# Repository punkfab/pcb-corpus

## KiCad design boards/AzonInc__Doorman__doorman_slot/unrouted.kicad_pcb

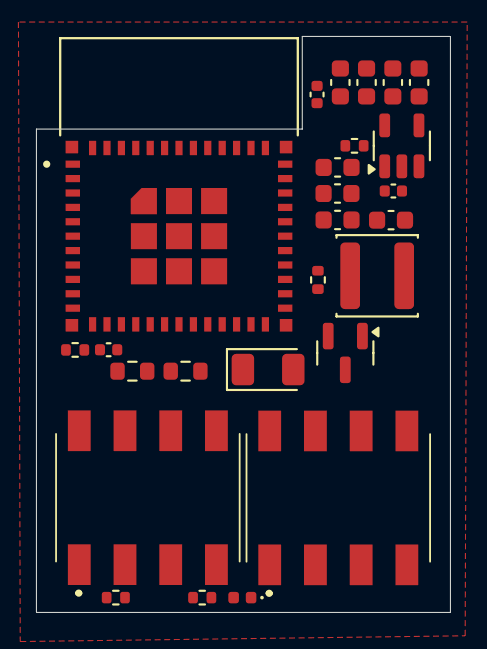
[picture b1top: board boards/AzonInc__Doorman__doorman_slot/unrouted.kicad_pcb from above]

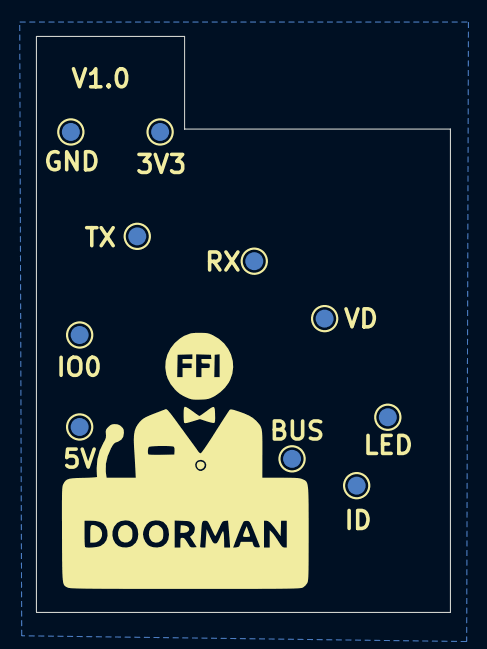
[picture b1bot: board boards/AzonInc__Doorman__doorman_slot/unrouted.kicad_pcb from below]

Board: 4 copper layers, 23.0 x 32.0 mm, 36 parts (10 on the bottom side), 22 nets, no tracks yet.

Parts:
C1, C2, C3, C4, C6, C7, C8, C9: 20uF; C_0603_1608Metric
C5, C11: 100nF; C_0402_1005Metric
C10: 20uF; C_0402_1005Metric
D1: Red; LED_0402_1005Metric
D2: D_Zener; D_1206_3216Metric
J2, J3: 70AAJ-4-M0; 70AAJ4M0
L1: TBD; L_APV_ANR4010
Q1: BC817; SOT-23
R1: 2.2K; R_0402_1005Metric
R3, R5: 10K; R_0402_1005Metric
R6: 600; R_0402_1005Metric
R7: 1M; R_0603_1608Metric
R8: 160K; R_0603_1608Metric
R9: 1K; R_0402_1005Metric
TP1: RX TestPoint; TestPoint_Pad_D1.0mm
TP2: TX TestPoint; TestPoint_Pad_D1.0mm
TP3: 3.3V TestPoint; TestPoint_Pad_D1.0mm
TP4: 5V TestPoint; TestPoint_Pad_D1.0mm
TP5: LED TestPoint; TestPoint_Pad_D1.0mm
TP6: Identity TestPoint; TestPoint_Pad_D1.0mm
TP7: VD TestPoint; TestPoint_Pad_D1.0mm
TP8: BUS TestPoint; TestPoint_Pad_D1.0mm
TP9: GND TestPoint; TestPoint_Pad_D1.0mm
TP10: GPIO0 TestPoint; TestPoint_Pad_D1.0mm
U2: XC6210B332MR; SOT-23-5
U3: ESP32-PICO-MINI-02; MODULE_ESP32-PICO-MINI-02

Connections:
+3.3V: C6.1, C7.1, C8.1, C9.1, C10.1, R5.1, TP3.1, U2.5 (VOUT), U3.3 (3V3)
+5V: J3.5, L1.1, TP4.1
GND: C1.1, C2.2, C3.2, C4.2, C5.1, C6.2, C7.2, C8.2, C9.2, C10.2, C11.1, D1.1 (K), J2.1, J2.8, Q1.2 (E), R1.1, R8.1, TP9.1, U2.2 (GND), U3.1 (GND), U3.2 (GND), U3.11 (GND), U3.14 (GND), U3.36 (GND), U3.37 (GND), U3.38 (GND), U3.39 (GND), U3.40 (GND), U3.41 (GND), U3.42 (GND), U3.43 (GND), U3.44 (GND), U3.45 (GND), U3.46 (GND), U3.47 (GND), U3.48 (GND), U3.49 (GND), U3.50 (GND), U3.51 (GND), U3.52 (GND), U3.53 (GND), U3.54 (GND), U3.55 (GND), U3.56 (GND), U3.57 (GND), U3.58 (GND), U3.59 (GND), U3.60 (GND), U3.61 (GND)
GPIO0: TP10.1, U3.23 (IO0)
GPIO4: R9.1, U3.24 (IO4)
GPIO12: J3.8, U3.19 (IO12)
GPIO13: J3.7, U3.20 (IO13)
GPIO14: J2.5, U3.18 (IO14)
GPIO15: J3.6, U3.21 (IO15)
GPIO26: R7.2, R8.2, TP7.1, U3.16 (IO26)
GPIO27: R6.2, TP5.1, U3.17 (IO27)
IDENTITY: J2.2, R1.2
unnamed: D1.2 (A), R6.1
unnamed: D2.2 (A), Q1.3 (C)
unnamed: J2.7, TP6.1
unnamed: Q1.1 (B), R9.2
unnamed: R3.2, U2.3 (CE)
unnamed: C1.2, C2.1, C3.1, C4.1, C5.2, L1.2, R3.1, U2.1 (VIN)
unnamed: C11.2, R5.2, U3.8 (EN)
RX: TP2.1, U3.30 (RXD0)
TASTA_ONLY_BUS: D2.1 (K), J2.6, R7.1, TP8.1
TX: TP1.1, U3.31 (TXD0)

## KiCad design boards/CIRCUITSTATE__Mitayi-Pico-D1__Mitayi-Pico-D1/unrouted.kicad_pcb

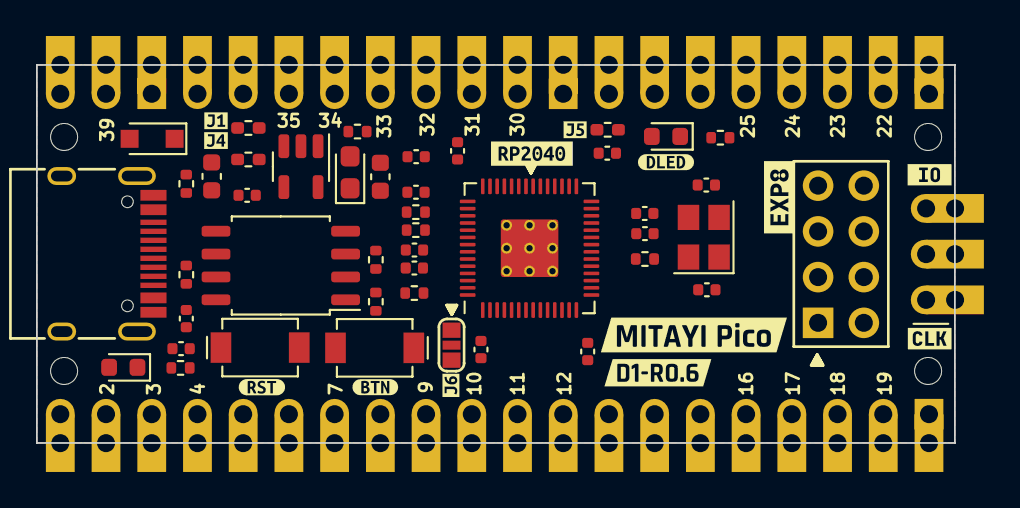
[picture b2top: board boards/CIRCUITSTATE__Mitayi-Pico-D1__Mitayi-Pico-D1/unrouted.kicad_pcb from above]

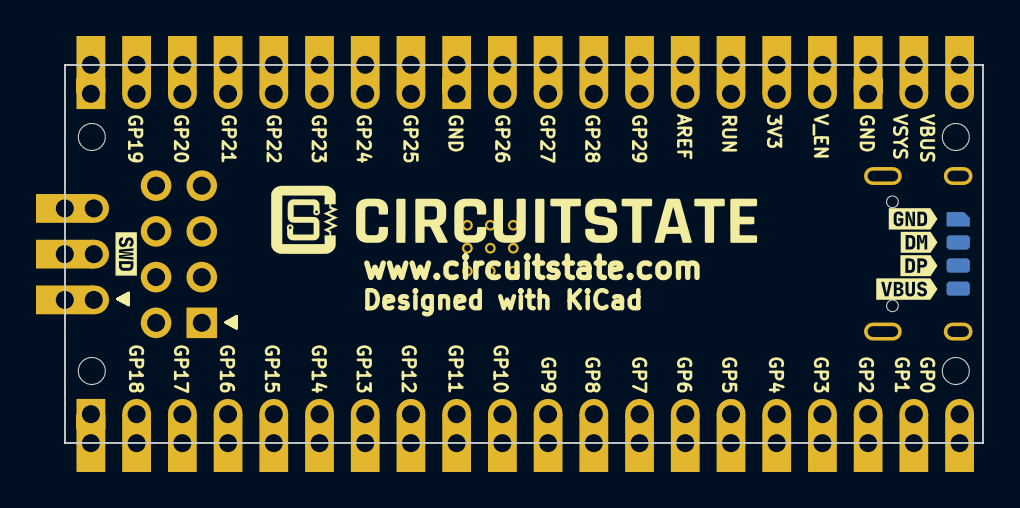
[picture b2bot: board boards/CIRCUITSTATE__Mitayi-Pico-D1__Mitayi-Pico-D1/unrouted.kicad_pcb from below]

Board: 2 copper layers, 51.0 x 21.0 mm, 73 parts (11 on the bottom side), 61 nets, no tracks yet.

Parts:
C1, C2, C6, C7, C8, C9, C10, C11, C12: 0.1uF; C_0402_1005Metric
C4, C5, C19: 1uF; C_0402_1005Metric
C13, C15: 10uF; C_0603_1608Metric
C14: 2.2uF; CP_EIA-2012-12_Kemet-R
C16: 470pF; C_0402_1005Metric
C17, C18: 30pF; C_0402_1005Metric
D1: BS5817WS; D_SOD-323_HandSoldering
D2: BLUE; LED_0603_1608Metric
D3: RED; LED_0603_1608Metric
H1, H2, H3, H4: MountingHole; MountingHole_2.2mm_M2
J1: EXP8; PinHeader_2x04_P2.54mm_Vertical
J2: USB-C-2.0; USB_C_Receptacle_HRO_TYPE-C-31-M-12
J3: Header-1; PinHeader_1x20_2H_P2.54mm_Vertical
J4: Header-2; PinHeader_1x20_2H_P2.54mm_Vertical
J5: SWD; PinHeader_1x03_P2.54mm_Vertical
J7: VBUS; Solderpad_Rounded_Rectangle_0.8x1.3mm
J8: DM; Solderpad_Rounded_Rectangle_0.8x1.3mm
J9: DP; Solderpad_Rounded_Rectangle_0.8x1.3mm
J10: GND; Solderpad_Rectangle_0.8x1.3mm_Chamfered
JP1, JP4, JP5: 0R; R_0402_1005Metric_Pad0.72x0.64mm_HandSolder
JP6: BTN_SEL; SolderJumper-3_P0.83mm_Open_Rounded-Pad_0.85x1mm
R1: DNP; R_0402_1005Metric
R2, R10: 1K; R_0402_1005Metric
R3, R4, R11: 5.1K; R_0402_1005Metric
R5, R6: 27R; R_0402_1005Metric
R7, R8: 470R; R_0402_1005Metric
R9: 10K; R_0402_1005Metric
SW1, SW2: UK-B0273-SP25Y; CK_SW_SPST_UK-B0273-SP25Y
U1: W25Q32JVSSIQ; SOIC-8_5.23x5.23mm_P1.27mm
U2: MIC5219-3.3YM5; SOT-23-5
U3: RP2040; RP2040-QFN-56
Y1: YIC-12M20P2/XT324-10/10; Crystal_SMD_3225-4Pin_3.2x2.5mm
kibuzzard-66CE1AA2: G***; kibuzzard-66CE1AA2
kibuzzard-66CE1AF9: G***; kibuzzard-66CE1AF9
kibuzzard-631DCCC7: G***; kibuzzard-631DCCC7
kibuzzard-631DCD0C: G***; kibuzzard-631DCD0C
kibuzzard-631DCDA0: G***; kibuzzard-631DCDA0
kibuzzard-631DCDB3: G***; kibuzzard-631DCDB3
kibuzzard-631DCE60: G***; kibuzzard-631DCE60
kibuzzard-632CA15B: G***; kibuzzard-632CA15B
kibuzzard-660C3D9D: G***; kibuzzard-660C3D9D
kibuzzard-680DBD8D: G***; kibuzzard-680DBD8D
kibuzzard-680DBD83: G***; kibuzzard-680DBD83
kibuzzard-680DBD88: G***; kibuzzard-680DBD88
kibuzzard-680DBD96: G***; kibuzzard-680DBD96
kibuzzard-680DBDCE: G***; kibuzzard-680DBDCE
kibuzzard-680DBDF9: G***; kibuzzard-680DBDF9
kibuzzard-680DC314: G***; kibuzzard-680DC314
kibuzzard-680DC361: G***; kibuzzard-680DC361
kibuzzard-66126165: G***; kibuzzard-66126165

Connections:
+1V1: C2.1, C4.1, U3.23 (DVDD), U3.45 (VREG-VOUT), U3.50 (DVDD)
+3V3: C1.1, C5.1, C6.1, C7.1, C8.1, C9.1, C10.1, C11.1, C12.1, C14.1, C15.1, D3.2 (A), J1.2, J4.5, JP1.2 (B), R1.1, R9.1, R11.2, U1.8 (VCC), U2.5 (OUT), U3.1 (IOVDD), U3.10 (IOVDD), U3.22 (IOVDD), U3.33 (IOVDD), U3.42 (IOVDD), U3.44 (VREG-VIN), U3.48 (USB-VDD), U3.49 (IOVDD)
/AREF: J4.6, JP1.1 (A), U3.43 (ADC-AVDD)
/GPIO0: J3.1, U3.2 (GPIO0)
/GPIO1: J3.2, U3.3 (GPIO1)
/GPIO2: J3.3, JP6.3 (B), R11.1, U3.4 (GPIO2)
/GPIO3: J3.4, U3.5 (GPIO3)
/GPIO4: J3.5, U3.6 (GPIO4)
/GPIO5: J3.6, U3.7 (GPIO5)
/GPIO6: J3.7, U3.8 (GPIO6)
/GPIO7: J3.8, U3.9 (GPIO7)
/GPIO8: J1.7, J3.9, U3.11 (GPIO8)
/GPIO9: J1.8, J3.10, U3.12 (GPIO9)
/GPIO10: J3.11, U3.13 (GPIO10)
/GPIO11: J3.12, U3.14 (GPIO11)
/GPIO12: J1.3, J3.13, U3.15 (GPIO12)
/GPIO13: J1.4, J3.14, U3.16 (GPIO13)
/GPIO14: J1.6, J3.15, U3.17 (GPIO14)
/GPIO15: J1.5, J3.16, U3.18 (GPIO15)
/GPIO16: J3.17, U3.27 (GPIO16)
/GPIO17: J3.18, U3.28 (GPIO17)
/GPIO18: J3.19, U3.29 (GPIO18)
/GPIO19: J4.19, U3.30 (GPIO19)
/GPIO20: J4.18, U3.31 (GPIO20)
/GPIO21: J4.17, U3.32 (GPIO21)
/GPIO22: J4.16, U3.34 (GPIO22)
/GPIO23: J4.15, U3.35 (GPIO23)
/GPIO24: J4.14, U3.36 (GPIO24)
/GPIO25: J4.13, JP5.1 (A), U3.37 (GPIO25)
/GPIO26: J4.11, U3.38 (GPIO26/ADC0)
/GPIO27: J4.10, U3.39 (GPIO27/ADC1)
/GPIO28: J4.9, U3.40 (GPIO28/ADC2)
/GPIO29: J4.8, U3.41 (GPIO29/ADC3)
/QSPI_SCLK: U1.6 (CLK), U3.52 (QSPI-SCLK)
/QSPI_SD0: U1.5 (DI(IO0)), U3.53 (QSPI-SD0)
/QSPI_SD1: U1.2 (DO(IO1)), U3.55 (QSPI-SD1)
/QSPI_SD2: U1.3 (IO2), U3.54 (QSPI-SD2)
/QSPI_SD3: U1.7 (IO3), U3.51 (QSPI-SD3)
/QSPI_SS: R1.2, R2.1, U1.1 (~CS), U3.56 (QSPI-SS-N)
/RUN: C19.1, J4.7, R9.2, SW1.1, U3.26 (RUN)
/SWCLK: J5.1, U3.24 (SWCLK)
/SWDIO: J5.3, U3.25 (SWDIO)
/USB_D+: J2.A6 (D+), J2.B6 (D+), J9.1, R5.1
/USB_D-: J2.A7 (D-), J2.B7 (D-), J8.1, R6.1
/VSYS: C13.1, D1.1 (K), J4.2, JP4.1 (A), U2.1 (IN)
/V_EN: J4.4, JP4.2 (B), U2.3 (EN)
/XIN: C17.1, U3.20 (XIN), Y1.1
/XOUT: R10.1, U3.21 (XOUT)
/~USB_BOOT: JP6.1 (A), R2.2
GND: C1.2, C2.2, C4.2, C5.2, C6.2, C7.2, C8.2, C9.2, C10.2, C11.2, C12.2, C13.2, C14.2, C15.2, C16.2, C17.2, C18.2, C19.2, J1.1, J2.A1 (GND), J2.A12 (GND), J2.B1 (GND), J2.B12 (GND), J2.S1 (SHIELD), J3.20, J4.3, J4.12, J4.20, J5.2, J10.1, R3.2, R4.2, R7.1, R8.1, SW1.2, SW2.2, U1.4 (GND), U2.2 (GND), U3.19 (TESTEN), U3.57 (GND), Y1.2, Y1.4
unnamed: C18.1, R10.2, Y1.3
unnamed: D2.2 (A), JP5.2 (B)
unnamed: D2.1 (K), R7.2
unnamed: D3.1 (K), R8.2
unnamed: J2.A5 (CC1), R3.1
unnamed: J2.B5 (CC2), R4.1
unnamed: JP6.2 (C), SW2.1
unnamed: C16.1, U2.4 (BP)
unnamed: R6.2, U3.46 (USB-DM)
unnamed: R5.2, U3.47 (USB-DP)
VBUS: D1.2 (A), J2.A4 (VBUS), J2.A9 (VBUS), J2.B4 (VBUS), J2.B9 (VBUS), J4.1, J7.1

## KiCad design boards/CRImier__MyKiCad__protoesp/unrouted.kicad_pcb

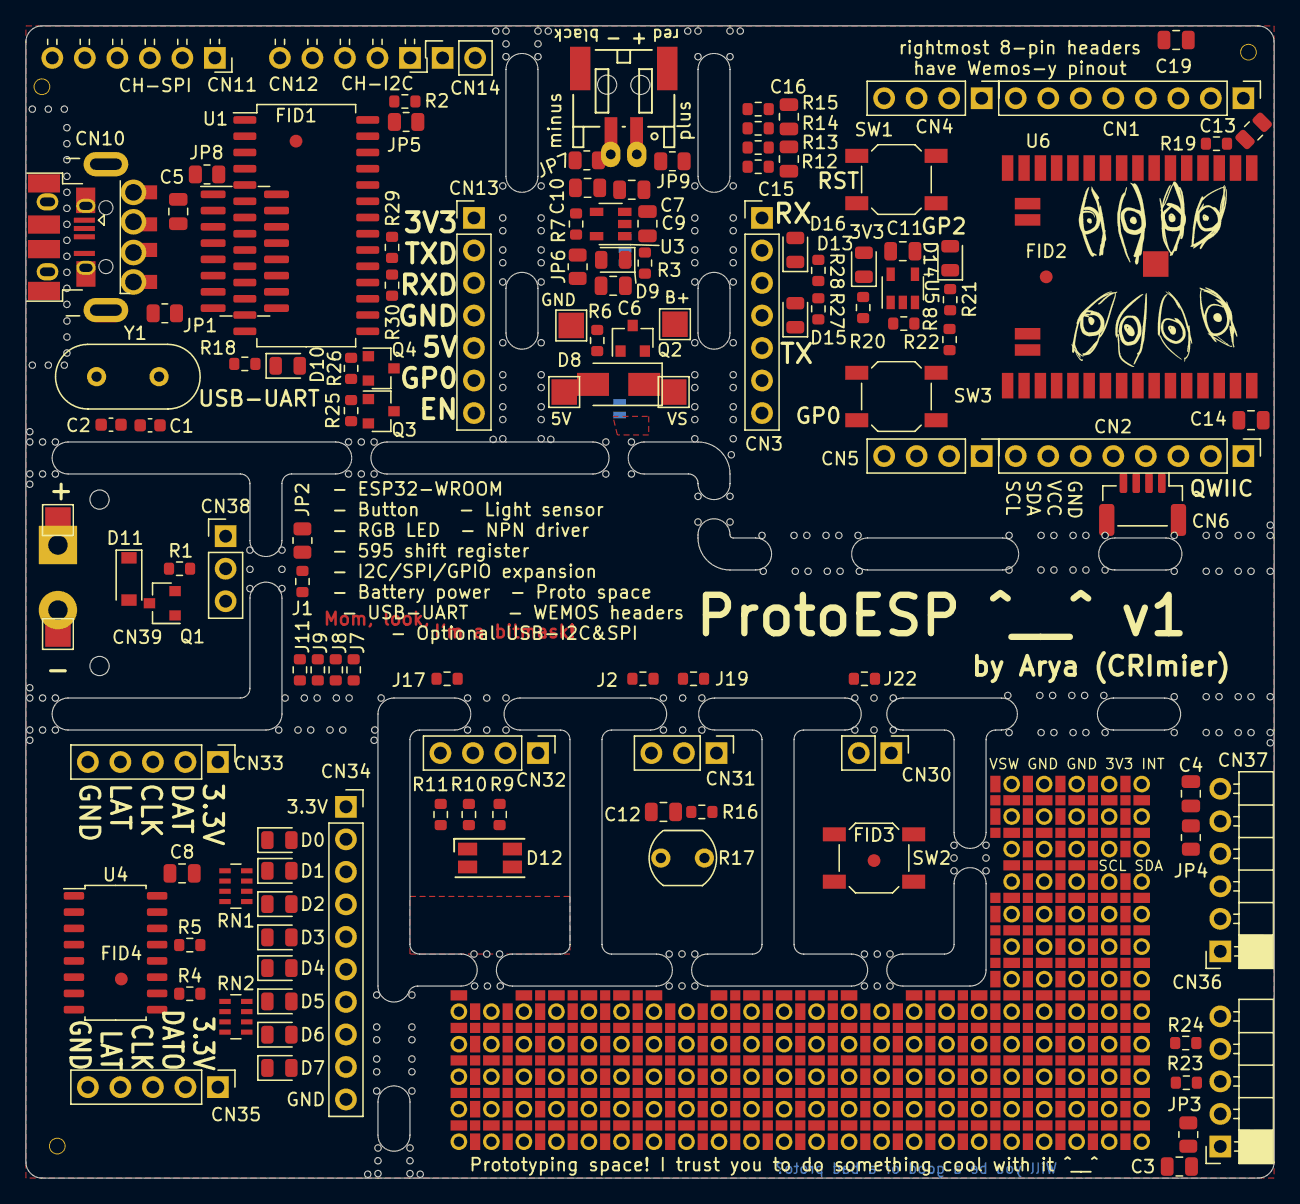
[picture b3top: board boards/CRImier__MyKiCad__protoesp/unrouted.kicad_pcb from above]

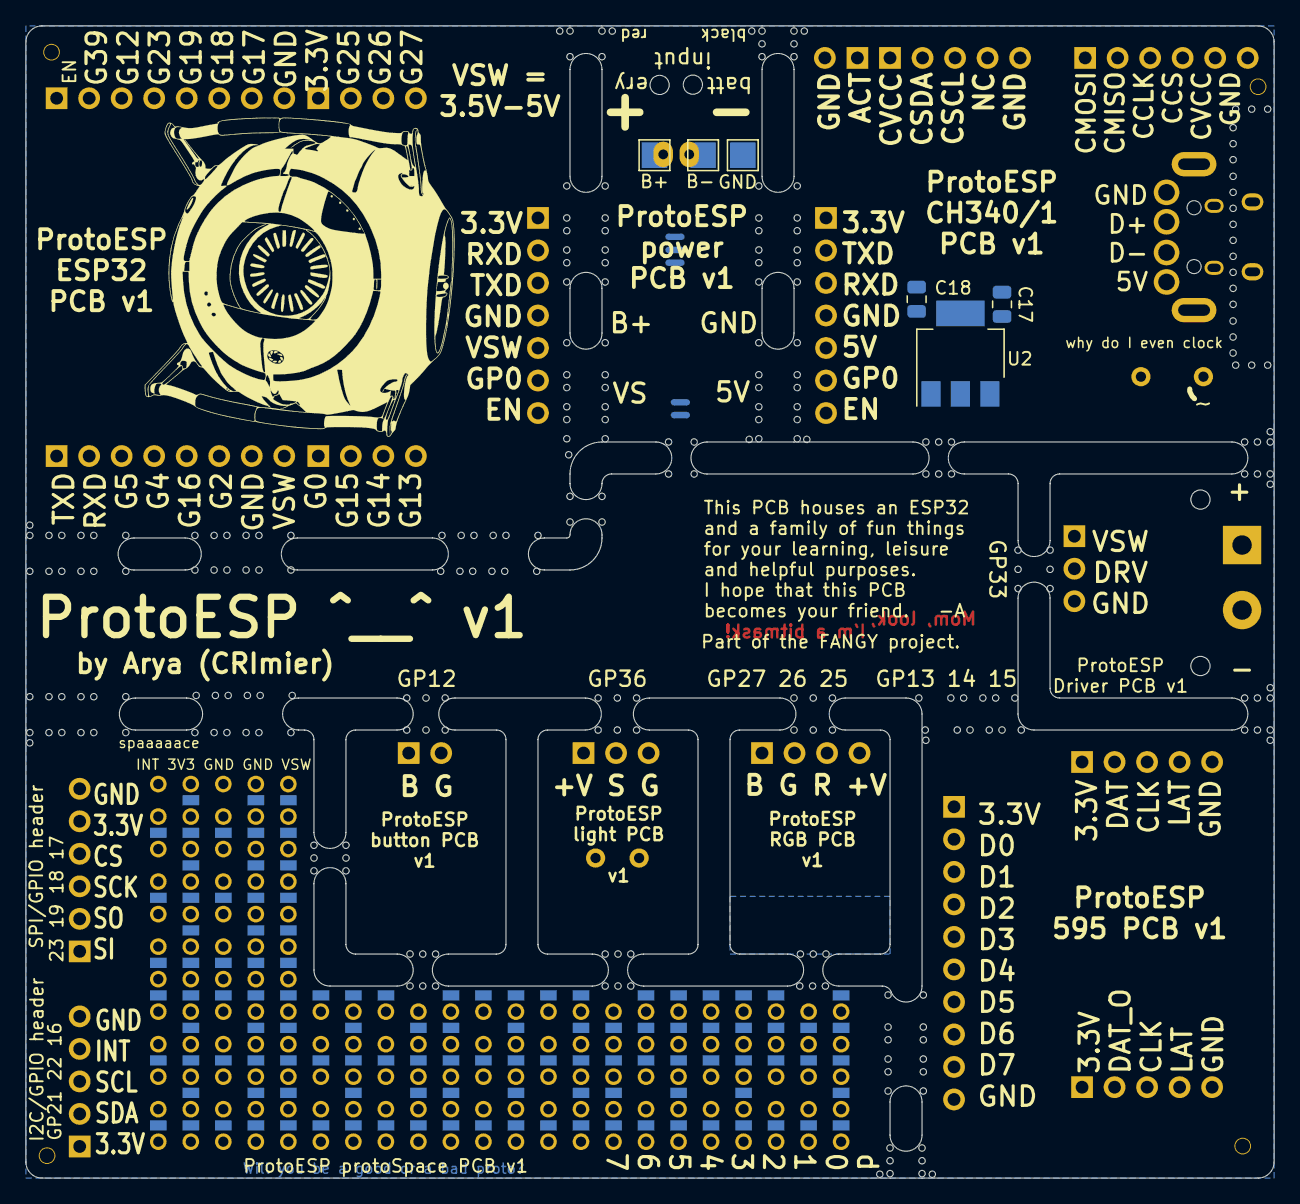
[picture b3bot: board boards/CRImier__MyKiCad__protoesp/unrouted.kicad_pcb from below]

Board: 2 copper layers, 97.5 x 90.0 mm, 149 parts (11 on the bottom side), 104 nets, no tracks yet.

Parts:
C1, C2: 18pF; C_0603_1608Metric
C3, C4, C5, C7, C8, C11, C12, C14, C15, C16, C17, C18, C19: 100nF; C_0805_2012Metric
C6, C9, C10, C13: 1uF; C_0805_2012Metric
CN1: EPINS_TOP; PinHeader_1x08_P2.54mm_Vertical
CN2: EPINS_BOTTOM; PinHeader_1x08_P2.54mm_Vertical
CN3: ESP_PROG; PinHeader_1x07_P2.54mm_Vertical
CN4: EPINS_TOP_E; PinHeader_1x04_P2.54mm_Vertical
CN5: EPINS_BOTTOM_E; PinHeader_1x04_P2.54mm_Vertical
CN6: QWIIC; JST_SH_BM04B-SRSS-TB_1x04-1MP_P1.00mm_Vertical
CN10: USB_CURSED; USB_Combined
CN11: CH_SPI; PinSocket_1x06_P2.54mm_Horizontal
CN12: CH_I2C; PinSocket_1x05_P2.54mm_Horizontal
CN13: CH341_PROG; PinHeader_1x07_P2.54mm_Vertical
CN14: CH_PROG; PinSocket_1x02_P2.54mm_Vertical
CN20: BATT; JST_PH_S2B-PH-SM4-TB_02x2.00mm_Angled
CN30: BUTTON_CONN; PinHeader_1x02_P2.54mm_Vertical
CN31: LDR_CONN; PinHeader_1x03_P2.54mm_Vertical
CN32: RGB_CONN; PinHeader_1x04_P2.54mm_Vertical
CN33: 595_CONN; PinHeader_1x05_P2.54mm_Vertical
CN34: 595_OUTS; PinSocket_1x10_P2.54mm_Vertical
CN35: 595CHAIN_CONN; PinHeader_1x05_P2.54mm_Vertical
CN36: E_I2C; PinSocket_1x05_P2.54mm_Horizontal
CN37: E_SPI; PinSocket_1x06_P2.54mm_Horizontal
CN38: DRV_CONN; PinHeader_1x03_P2.54mm_Vertical
CN39: DRV; TerminalBlock_bornier-2_P5.08mm
D0, D1, D2, D3, D4, D5, D6, D7: LED; LED_0805_2012Metric
D8: SS14; D_SMA
D9: LED_CHG; LED_0805_2012Metric
D10: LED_5V; LED_0805_2012Metric
D11: 1N4148; D_SOD-123
D12: LED_RGBA; LED_RGB_1210
D13: LED_3V3; LED_0805_2012Metric
D14: LED_ESP; LED_0805_2012Metric
D15: LED_TX; LED_0805_2012Metric
D16: LED_RX; LED_0805_2012Metric
FID1, FID2, FID3, FID4: Fiducial; Fiducial_1mm_Mask2mm
H1, H1#2, H1#3, H1#5: pin_hole; PinHole_1,5mm
H1#4, H4: MountingHole; JLCPCBToolingHole
H2, H3: ToolingHole; JLCPCBToolingHole
J1, J2, J7, J8, J9, J11, J17, J19, J22: 0R; R_0603_1608Metric
JP1, JP2, JP3, JP4, JP5, JP7, JP8, JP9: 0R; R_0805_2012Metric
JP6: F; R_0805_2012Metric
NT1, NT2, NT3, NT6, NT7: Net-Tie_2; NetTie-2_SMD_Pad0.5mm
P1: PROTO_SPACE; PROTO_THT_SMD_FULL
Q1, Q3, Q4: BC817; SOT-23
Q2: CJ2305; SOT-23
R1, R2, R3, R4, R5, R6, R18, R20, R21, R23, R24, R27, R28, R29, R30: 1K8; R_0603_1608Metric
R7, R8, R16, R19, R22, R25, R26: 4K7; R_0603_1608Metric
R9: RGB_R_B; R_0603_1608Metric
R10: RGB_R_G; R_0603_1608Metric
R11: RGB_R_R; R_0603_1608Metric
R12, R13, R14, R15: 47K; R_0603_1608Metric
R17: LDR07; R_LDR_5.1x4.3mm_P3.4mm_Vertical
RN1, RN2: R_Pack04; R_Array_Concave_4x0603
SW1: EN; SW_SPST_SKQG_WithStem
SW2: BUTTON; SW_SPST_SKQG_WithStem
SW3: GP0; SW_SPST_SKQG_WithStem
TP1: +; TestPoint_Pad_2.0x2.0mm
TP2: -; TestPoint_Pad_2.0x2.0mm
TP3, TP8: B+; TestPoint_Pad_2.0x2.0mm
TP4: 5V; TestPoint_Pad_2.0x2.0mm
TP5, TP9: GND; TestPoint_Pad_2.0x2.0mm
TP6: VS; TestPoint_Pad_2.0x2.0mm
TP7: B-; TestPoint_Pad_2.0x2.0mm
U1: CH341; SOIC-28W_SOIC16_CH34x_Combined
U2: AP1117-33; SOT-223-3_TabPin2
U3: LTH7R; SOT-23-5
U4: 74HC595; SOP-16_4.55x10.3mm_P1.27mm
U5: AP2112K-3.3; SOT-23-5
U6: ESP32-WROOM-32
Y1: 12MHz; Crystal_HC49-U_Vertical

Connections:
595_CLK: CN5.3, J9.1, U6.13 (IO14)
595_CLK_J: CN33.3, CN35.3, J9.2, U4.11 (SRCLK)
595_DAT: CN5.4, J8.1, U6.16 (IO13)
595_DAT_J: CN33.2, J8.2, U4.14 (SER)
595_DAT_O: CN35.2, U4.9 (QH')
595_LAT: CN5.2, J11.1, U6.23 (IO15)
595_LAT_J: CN33.4, CN35.4, J11.2, U4.12 (RCLK)
+3V3: C11.1, C13.1, C14.1, C18.1, CN1.8, CN3.1, CN6.2, CN13.1, D13.2 (A), D14.2 (A), D15.2 (A), D16.2 (A), J2.2, J7.1, J17.2, JP3.1, JP4.1, JP5.2, NT1.1, NT1.2, P1.d, R19.1, R22.2, R23.2, R24.2, U2.2 (VO), U5.5 (VOUT), U6.2 (VDD)
+5V: C6.1, C17.1, CN13.5, D8.2 (A), D10.2 (A), JP1.1, JP6.1, Q2.1 (G), R6.2, TP4.1, U2.3 (VI)
+BATT: C9.1, JP9.1, Q2.3 (D), R15.2, TP3.1, U3.3 (BAT)
+VSW: CN2.8, CN3.5, D8.1 (K), JP2.1, P1.a, Q2.2 (S), R8.1, TP6.1, U5.1 (VIN)
-BATT: CN20.2, JP7.1, TP7.1
/5D0: CN34.2, D0.2 (A), P1.d0, U4.15 (QA)
/5D1: CN34.3, D1.2 (A), P1.d1, U4.1 (QB)
/5D2: CN34.4, D2.2 (A), P1.d2, U4.2 (QC)
/5D3: CN34.5, D3.2 (A), P1.d3, U4.3 (QD)
/5D4: CN34.6, D4.2 (A), P1.d4, U4.4 (QE)
/5D5: CN34.7, D5.2 (A), P1.d5, U4.5 (QF)
/5D6: CN34.8, D6.2 (A), P1.d6, U4.6 (QG)
/5D7: CN34.9, D7.2 (A), P1.d7, U4.7 (QH)
/BUTTON_J: CN30.1, J22.2, SW2.1
/CH_XI: C1.1, U1.13 (XI), Y1.1
/CH_XO: C2.1, U1.14 (XO), Y1.2
/LIGHT_J: C12.1, CN31.2, J19.2, R16.1, R17.1
BATT_IN+: CN20.1, JP9.2, TP8.1
BUTTON: CN5.1, J22.1, U6.14 (IO12)
CHG_VIN: C7.1, C10.1, D9.2 (A), JP6.2, R12.2, U3.4 (VCC)
CH_ACT: CN14.1, R2.2
CH_CLK: CN11.3, U1.18 (~DCD/D3/SCK)
CH_CS: CN11.4, U1.15 (CS0/D0/~CTS)
CH_EN: CN13.7, NT7.1, Q3.3 (C)
CH_GP0: CN13.6, NT6.1, Q4.3 (C)
CH_MISO: CN11.2, U1.22 (~SLP/D7/DIN)
CH_MOSI: CN11.1, Q4.2 (E), R25.1, U1.20 (~DTR/D5/DOUT)
CH_RXD: CN13.3, NT3.1, R30.1
CH_SCL: CN12.3, U1.24 (SCL)
CH_SDA: CN12.2, U1.23 (SDA)
CH_TXD: CN13.2, NT2.1, R29.1
CH_V3: C5.1, JP8.2, U1.9 (V3)
CH_VCC: CN11.5, CN12.1, JP5.1, JP8.1, U1.28 (VCC)
CH_~RTS: CN12.4, Q3.2 (E), R26.1, U1.21 (~RTS/D6/DIN2)
D+: CN10.3 (D+), U1.10 (UD+)
D-: CN10.2 (D-), U1.11 (UD-)
DRIVER: J1.2, U6.9 (IO33)
DRV+: CN38.1, CN39.1, D11.1 (K), JP2.2, TP1.1
DRV-: CN39.2, D11.2 (A), Q1.3 (C), TP2.1
E_CS: CN1.7, CN37.4, U6.28 (IO17)
E_EN: C19.1, CN1.1, CN3.7, NT7.2, R19.2, SW1.2, U6.3 (EN)
E_GP0: CN3.6, NT6.2, R22.1, SW3.2, U6.25 (IO0)
E_INT: CN2.5, CN36.4, P1.e, U6.27 (IO16)
E_MISO: CN1.5, CN37.2, U6.31 (IO19)
E_MOSI: CN1.4, CN37.1, U6.37 (IO23)
E_RXD: CN2.2, CN3.2, NT2.2, R28.1, U6.34 (RXD0/IO3)
E_SCK: CN1.6, CN37.3, U6.30 (IO18)
E_SCL: CN6.4, CN36.3, P1.f, R24.1, U6.36 (IO22)
E_SDA: CN6.3, CN36.2, P1.g, R23.1, U6.33 (IO21)
E_TXD: CN2.1, CN3.3, NT3.2, R27.1, U6.35 (TXD0/IO1)
GND: C1.2, C2.2, C3.2, C4.2, C5.2, C6.2, C7.2, C8.2, C9.2, C10.2, C11.2, C12.2, C13.2, C14.2, C15.2, C16.2, C17.2, C18.2, C19.2, CN2.7, CN3.4, CN4.1, CN6.1, CN6.MP (MountPin), CN10.4 (GND), CN10.5 (Shield), CN11.6, CN12.5, CN13.4, CN14.2, CN20.MP (MountPin), CN30.2, CN31.3, CN33.5, CN34.10, CN35.5, CN36.5, CN37.6, CN38.3, JP7.2, P1.b, P1.c, Q1.2 (E), R5.1, R6.1, R7.1, R13.2, R14.2, R17.2, R18.1, R20.1, RN1.1 (R1.1), RN1.2 (R2.1), RN1.3 (R3.1), RN1.4 (R4.1), RN2.1 (R1.1), RN2.2 (R2.1), RN2.3 (R3.1), RN2.4 (R4.1), SW1.1, SW2.2, SW3.1, TP5.1, TP9.1, U1.12 (GND), U2.1 (GND), U3.2 (GND), U4.8 (GND), U5.2 (GND), U6.1 (GND), U6.15 (GND), U6.38 (GND), U6.39 (GND)
IO4: CN2.4, U6.26 (IO4)
IO5: CN2.3, U6.29 (IO5)
IO32: CN1.3, U6.8 (IO32)
IO39: CN1.2, U6.5 (SENSOR_VN)
LED_BLUE: CN4.4, CN32.1, R9.2, U6.12 (IO27)
LED_ESP: CN2.6, R21.1, U6.24 (IO2)
LED_GREEN: CN4.3, CN32.2, R10.2, U6.11 (IO26)
LED_RED: CN4.2, CN32.3, R11.2, U6.10 (IO25)
LED_VCC: CN32.4, D12.4 (A), J17.1
LIGHT: J19.1, U6.4 (SENSOR_VP)
unnamed: C3.1, CN36.1, JP3.2
unnamed: C4.1, CN37.5, JP4.2
unnamed: CN10.1 (VBUS), JP1.2
unnamed: CN31.1, J2.1, R16.2
unnamed: CN38.2, J1.1, R1.1
unnamed: D0.1 (K), RN1.8 (R1.2)
unnamed: D1.1 (K), RN1.7 (R2.2)
unnamed: D2.1 (K), RN1.6 (R3.2)
unnamed: D3.1 (K), RN1.5 (R4.2)
unnamed: D4.1 (K), RN2.8 (R1.2)
unnamed: D5.1 (K), RN2.7 (R2.2)
unnamed: D6.1 (K), RN2.6 (R3.2)
unnamed: D7.1 (K), RN2.5 (R4.2)
unnamed: D9.1 (K), R3.2
unnamed: D10.1 (K), R18.2
unnamed: D12.1 (RK), R11.1
unnamed: D12.2 (GK), R10.1
unnamed: D12.3 (BK), R9.1
unnamed: D13.1 (K), R20.2
unnamed: D14.1 (K), R21.2
unnamed: D15.1 (K), R27.2
unnamed: D16.1 (K), R28.2
unnamed: Q1.1 (B), R1.2
unnamed: Q3.1 (B), R25.2
unnamed: Q4.1 (B), R26.2
unnamed: R2.1, U1.1 (~ACT)
unnamed: R3.1, U3.1 (CHRG)
unnamed: R4.2, U4.10 (~SRCLR)
unnamed: R5.2, U4.13 (~OE)
unnamed: R7.2, U3.5 (PROG)
unnamed: R8.2, U5.3 (EN)
RXD: R30.2, U1.6 (RXD/PEMP)
TXD: R29.2, U1.5 (TXD/~ERR)
VBAT: C16.1, R14.1, R15.1, U6.7 (IO35)
VCC_595: C8.1, CN33.1, CN34.1, CN35.1, J7.2, R4.1, U4.16 (VCC)
VUSB: C15.1, R12.1, R13.1, U6.6 (IO34)

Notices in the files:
boards/CIRCUITSTATE__Mitayi-Pico-D1__Mitayi-Pico-D1/unrouted.kicad_pcb:
Released under MIT Open-source License
